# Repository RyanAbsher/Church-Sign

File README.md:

# Church Sign Controller

## Introduction
The **Church Sign Controller** is an ESP32-based wireless system designed to synchronize service status across multiple church buildings. This system allows a user in the main sanctuary to update the status of three remote signs in the nursery or classrooms, ensuring everyone is informed about the progress of the service.

## System Overview
The system utilizes the **ESP-NOW** protocol for communication between the controller and the signs. It supports four distinct states to communicate service progress:

* **Green:** Service is in progress.
* **Yellow:** Service is wrapping up (e.g., the band is on stage).
* **Red:** Service is over.
* **Off:** System is idle.

---

## Hardware Specifications

### The Controller
* **Module:** Built around an ESP32 with a touch display.
* **Interface:** Features an integrated LCD touchscreen for state selection.
* **Power:** Battery-powered with a dedicated wake button.
* **Power Management:** Enters sleep mode after 5 seconds of inactivity to conserve battery.

### The Signs
* **Module:** Based on ESP32 modules.
* **LEDs:** 12 WS2812B addressable LEDs per sign.
* **Power:** Powered by a 5V external power supply.

---

## Functional Behavior

### Controller GUI
* **Monitoring:** The screen is divided into three sections to show the current state, color, and communication status (including errors) for each sign.
* **Controls:** Includes four state buttons and a full-width "Save" button to store the current state in the controller's memory.
* **Sync:** All signs are updated to the same state simultaneously.

### Sign Animation & Logic
* **Visual Alerts:** When switching to Green, Yellow, or Red, the signs perform a flashing sequence before turning solid to ensure the change is noticed.
* **Idle Transition:** Switching to "Off" turns the LEDs off immediately without a flash pattern.
* **Safety Timeout:** Signs automatically turn off if they remain active for more than 8 hours.

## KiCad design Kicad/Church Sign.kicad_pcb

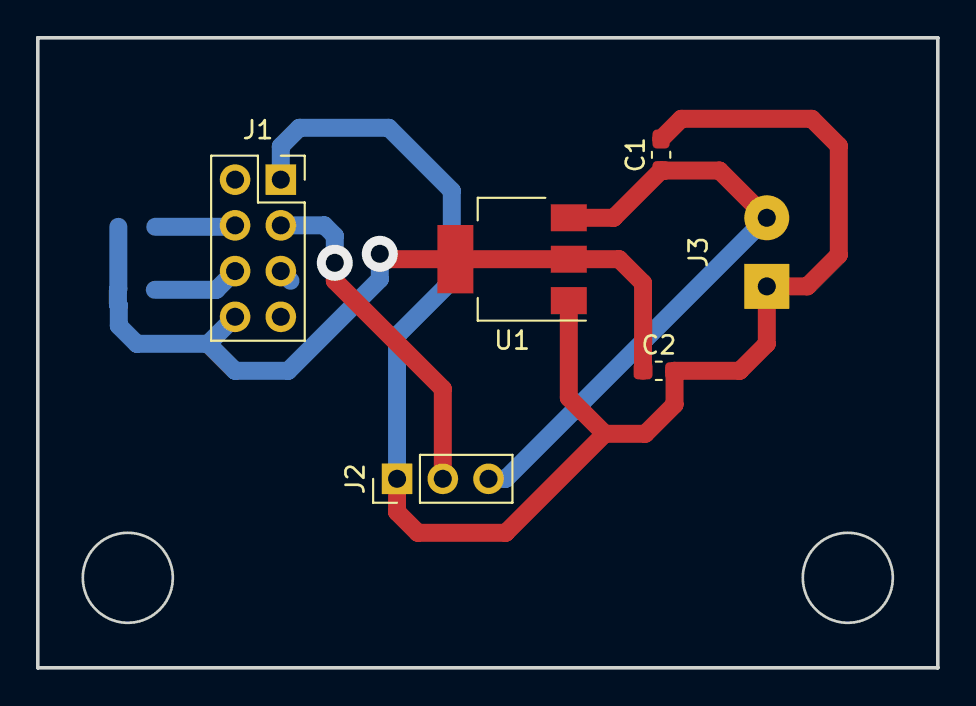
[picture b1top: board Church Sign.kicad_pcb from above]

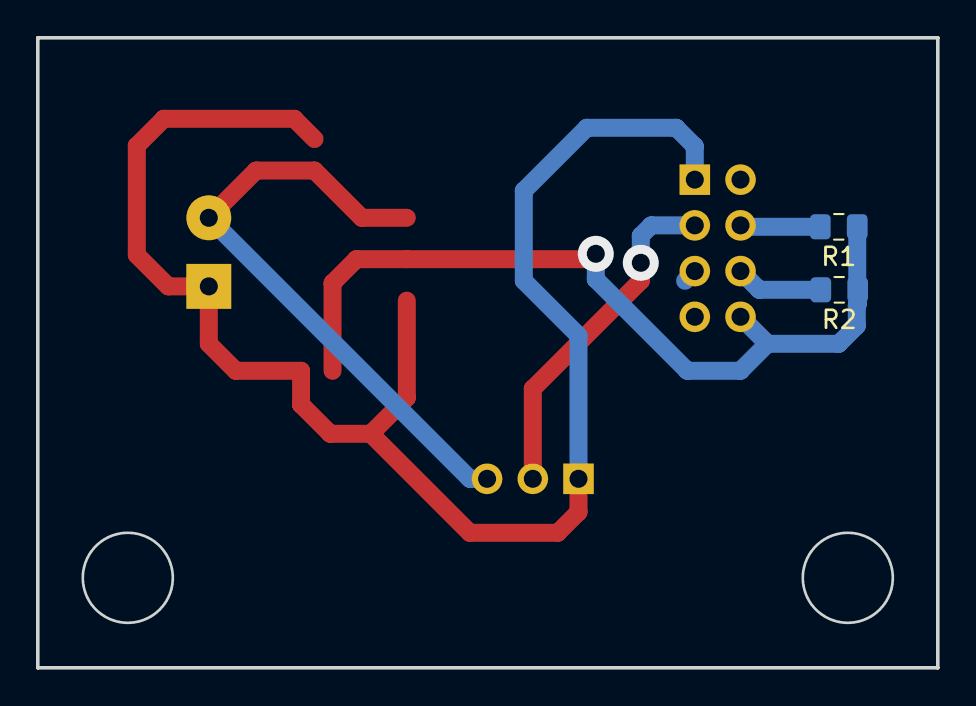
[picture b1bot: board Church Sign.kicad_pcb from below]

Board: 2 copper layers, 50.0 x 35.0 mm, 8 parts (2 on the bottom side), 6 nets.

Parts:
C1, C2: 0.1uF; C_0603_1608Metric_Pad1.05x0.95mm_HandSolder
J1: ESP Header; PinSocket_2x04_P2.54mm_Vertical
J2: To LEDs; PinHeader_1x03_P2.54mm_Vertical
J3: 5V In; SolderWirePad_1x02_P3.81mm_Drill1mm
R1, R2: 10k; R_0805_2012Metric_Pad1.15x1.40mm_HandSolder
U1: AZ1117-3.3; SOT-223-3_TabPin2

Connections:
+3V3: C2.1, J1.8, R1.1, R2.1, U1.2
+5V: C1.1, J2.3, J3.2, U1.3
/LED_DATA: J1.3, J2.2
GND: C1.2, C2.2, J1.1, J2.1, J3.1, U1.1
unnamed: J1.4, R1.2
unnamed: J1.6, R2.2

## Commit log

2020-07-24 Initial Commit
    I created a new blank KiCAD project, as the original project was lost. The original Arduino code was saved, and is includede here.
2020-07-24 Redesign
    Since the original design was lost, I completely redesigned the PCB. The newer design is much smaller and more compact. It uses a 2 layer board instead of a single layer.
2020-07-24 Changes
    Moved ESP header traces to back layer.
2020-07-24 Moved LED Pin
    Moved the LED data pin from IO0 to IO2.
2026-02-12 Updated the project description. Still need to upload new project files.
